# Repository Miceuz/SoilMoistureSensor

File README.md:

SoilMoistureSensor
==================

A Time Domain Reflectometry - based soil moisture sensor.

WORK IN PROGRESS

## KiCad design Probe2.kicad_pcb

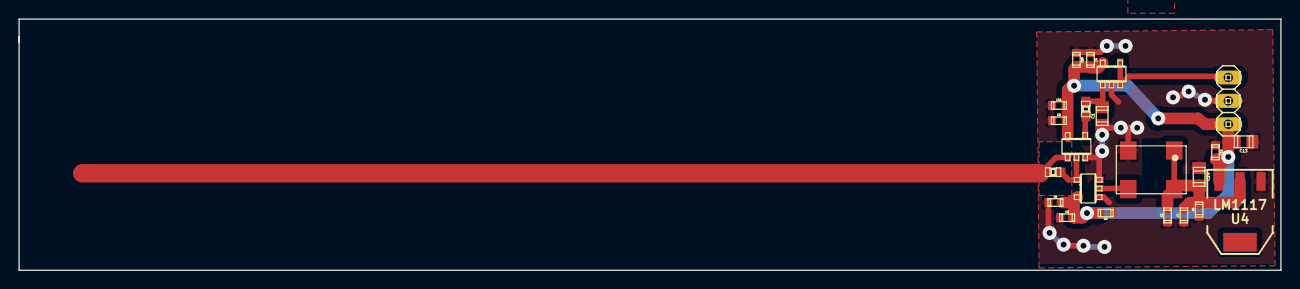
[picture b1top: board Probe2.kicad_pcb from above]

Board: 2 copper layers, 137.2 x 27.3 mm, 22 parts (0 on the bottom side), 9 nets.

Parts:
C1, C13, C14: 10uF; c_0805
C2, C3, C4, C5, C6, C7, C8, C9, C10, C11, C12: C_0603; c_0603
K1: CONN_3; pinhead-1-1X03
R1: R_0603; m-pad-2.1-0603
R2: 1k; m-pad-2.1-0603
U1: 74LVC1G86W5; m-pad-2.1-SOT23-5
U2: 74LVC1G125; m-pad-2.1-SOT23-5
U3: MCP6L01UT; m-pad-2.1-SOT23-5
U4: LM1117; SOT223
X1: OSCILLATORS-4; m-pad-2.1-CB3_CB3LV

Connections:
/3.3V: C2.1, C6.1, C7.1, C14.1, U4.2, X1.1, X1.4
/output: K1.3, U3.3, U3.4
/transmission_line: R1.2, U1.1
GND: C1.2, C2.2, C3.2, C4.2, C5.2, C6.2, C7.2, C8.2, C9.2, C10.2, C11.2, C12.2, C13.2, C14.2, K1.2, U1.3, U2.1, U2.3, U3.2, U4.1, X1.2
unnamed: R2.1, U1.4
unnamed: U2.2, X1.3
unnamed: R1.1, U1.2, U2.4
unnamed: C1.1, R2.2, U3.1
VCC: C3.1, C4.1, C5.1, C8.1, C9.1, C10.1, C11.1, C12.1, C13.1, K1.1, U1.5, U2.5, U3.5, U4.3

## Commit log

2014-10-06 add long forgotten last effort
